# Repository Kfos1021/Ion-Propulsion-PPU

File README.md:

# **Spacecraft Ion Propulsion Power Processing Unit**

This Ion Propulsion Power Processing Unit (PPU) is a simulation-first hardware and embedded software project 
that converts a standard 24 V DC spacecraft bus into four independently regulated power stages: a 50–100 V Boost/Flyback 
Beam supply and a 12–24 V Discharge supply .The architecture integrates closed-loop LTspice circuit modeling, a 8-state bare-metal
C++ safety state machine with active hardware interlocks, a Python dynamic thruster load simulator with a Software-in-the-Loop (SiL) 
socket interface, and a fully routed 2-layer KiCad  PCB layout validated to a Design Rule Check (DRC) pass.

**System Diagram of PPU**

**Beam Boost Converter Transient & Regulation Response**

**Buck Converter Regulation Response**

**Route Diagram**

**3D View of PPU**

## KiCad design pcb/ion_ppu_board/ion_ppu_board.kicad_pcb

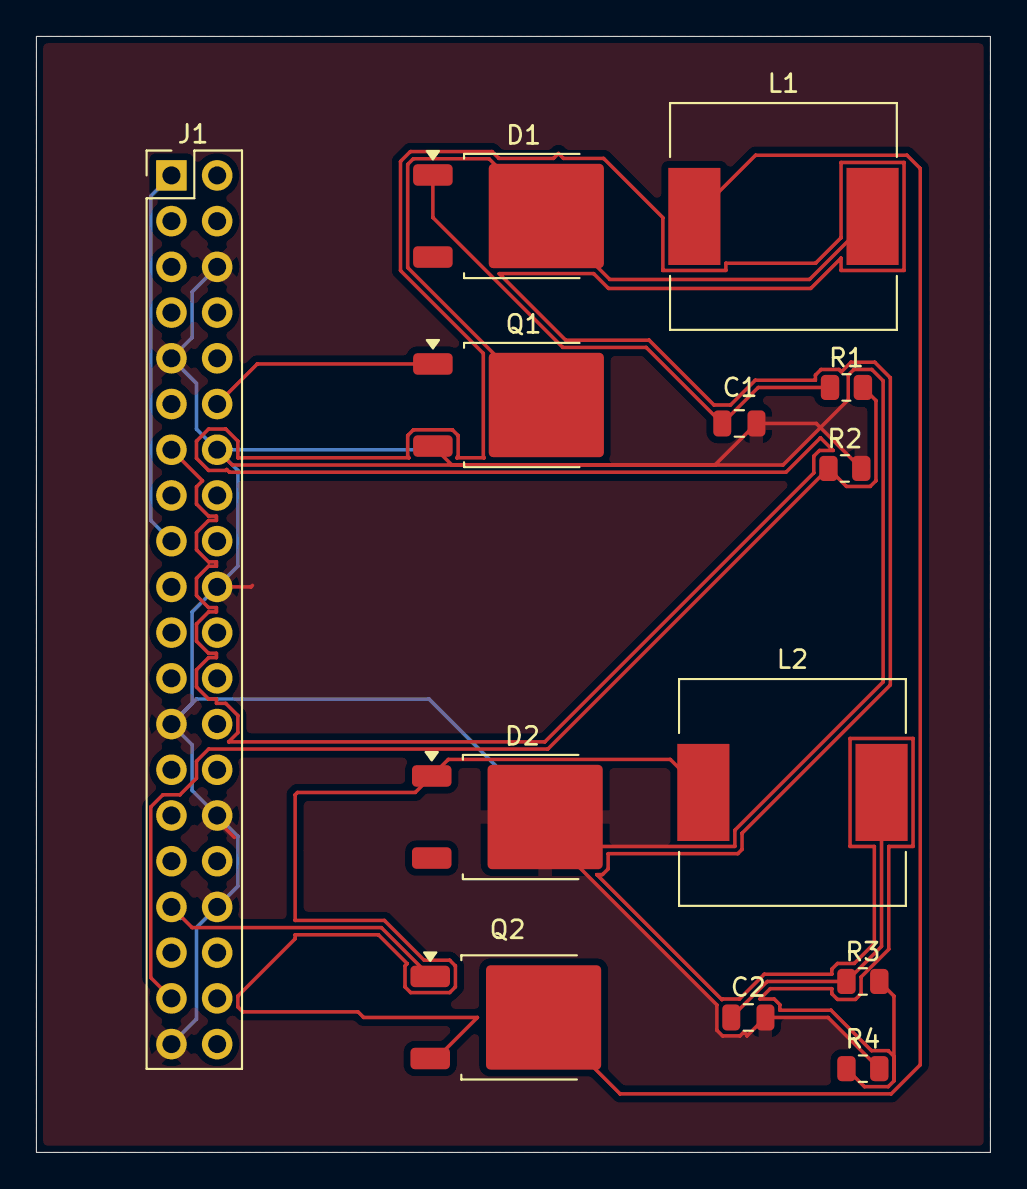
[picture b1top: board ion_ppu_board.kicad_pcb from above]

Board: 2 copper layers, 53.0 x 62.0 mm, 13 parts (0 on the bottom side), 11 nets.

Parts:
C1: 10uF; C_0805_2012Metric
C2: 22uF; C_0805_2012Metric
D1, D2: RB238NS150; TO-252-2
J1: Raspberry_Pi_2_3; PinHeader_2x20_P2.54mm_Vertical
L1: 1mh; L_12x12mm_H8mm
L2: 100uh; L_12x12mm_H8mm
Q1: IRFH5250; TO-252-2
Q2: Q_PMOS_GSD; TO-252-2
R1: 390k; R_0805_2012Metric
R2, R4: 10k; R_0805_2012Metric
R3: 50k; R_0805_2012Metric

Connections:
+15V_DISCHARGE: C2.1, L2.2, R3.1
+24V: L1.1, Q2.2 (S)
+100V_BEAM: C1.1, D1.1 (K), R1.1
/+3V3: J1.1 (3V3), J1.17 (3V3)
/FB_BEAM: J1.37 (GPIO26), R1.2, R2.1
/FB_DISCHARGE: J1.13 (GPIO27), R3.2, R4.1
/GATE_BEAM: J1.12 (GPIO18/PWM0), Q1.1 (G)
/GATE_DISCHARGE: J1.33 (PWM1/GPIO13), Q2.1 (G)
GND: C1.2, C2.2, D2.2 (A), J1.6 (GND), J1.9 (GND), J1.14 (GND), J1.20 (GND), J1.25 (GND), J1.30 (GND), J1.34 (GND), J1.39 (GND), Q1.3 (S), R2.2, R4.2
unnamed: D1.2 (A), L1.2, Q1.2 (D)
unnamed: D2.1 (K), L2.1, Q2.3 (D)
